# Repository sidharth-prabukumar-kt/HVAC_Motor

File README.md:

# HVAC Motor Project

## Overview

This project is centered around the development of an HVAC motor using a custom-designed motor controller PCB, crafted with KiCAD. The core of the software architecture is built on Zephyr RTOS, tailored with a customized device tree for optimal performance with the STM32 microcontroller.

## Features

- **Motor Control**: Utilizes PWM lines controlled by timer peripherals, interfacing with the TI *DRV8313* motor driver to manage a three-phase motor. This setup is enhanced with feedback mechanisms through current sense resistors and ADC, alongside hall effect sensors.
- **Temperature Regulation**: Incorporates a *LM75B* temperature sensor for data acquisition via I2C, regulating a surface's temperature. This surface is heated using a filament for testing purposes, simulating a real-world application.
- **Fan Implementation**: The three-phase motor is specifically deployed to drive a fan. This fan plays a role in cooling the aforementioned surface, ensuring the system remains within operational thermal limits.
- **Control Systems**: Implements two control systems:
    - A Field Oriented Control (FOC) system, leveraging feedback from the motor for precise PID loop control.
    - A temperature maintenance system, utilizing feedback from the temperature sensor to ensure the surface temperature remains within a designated range.

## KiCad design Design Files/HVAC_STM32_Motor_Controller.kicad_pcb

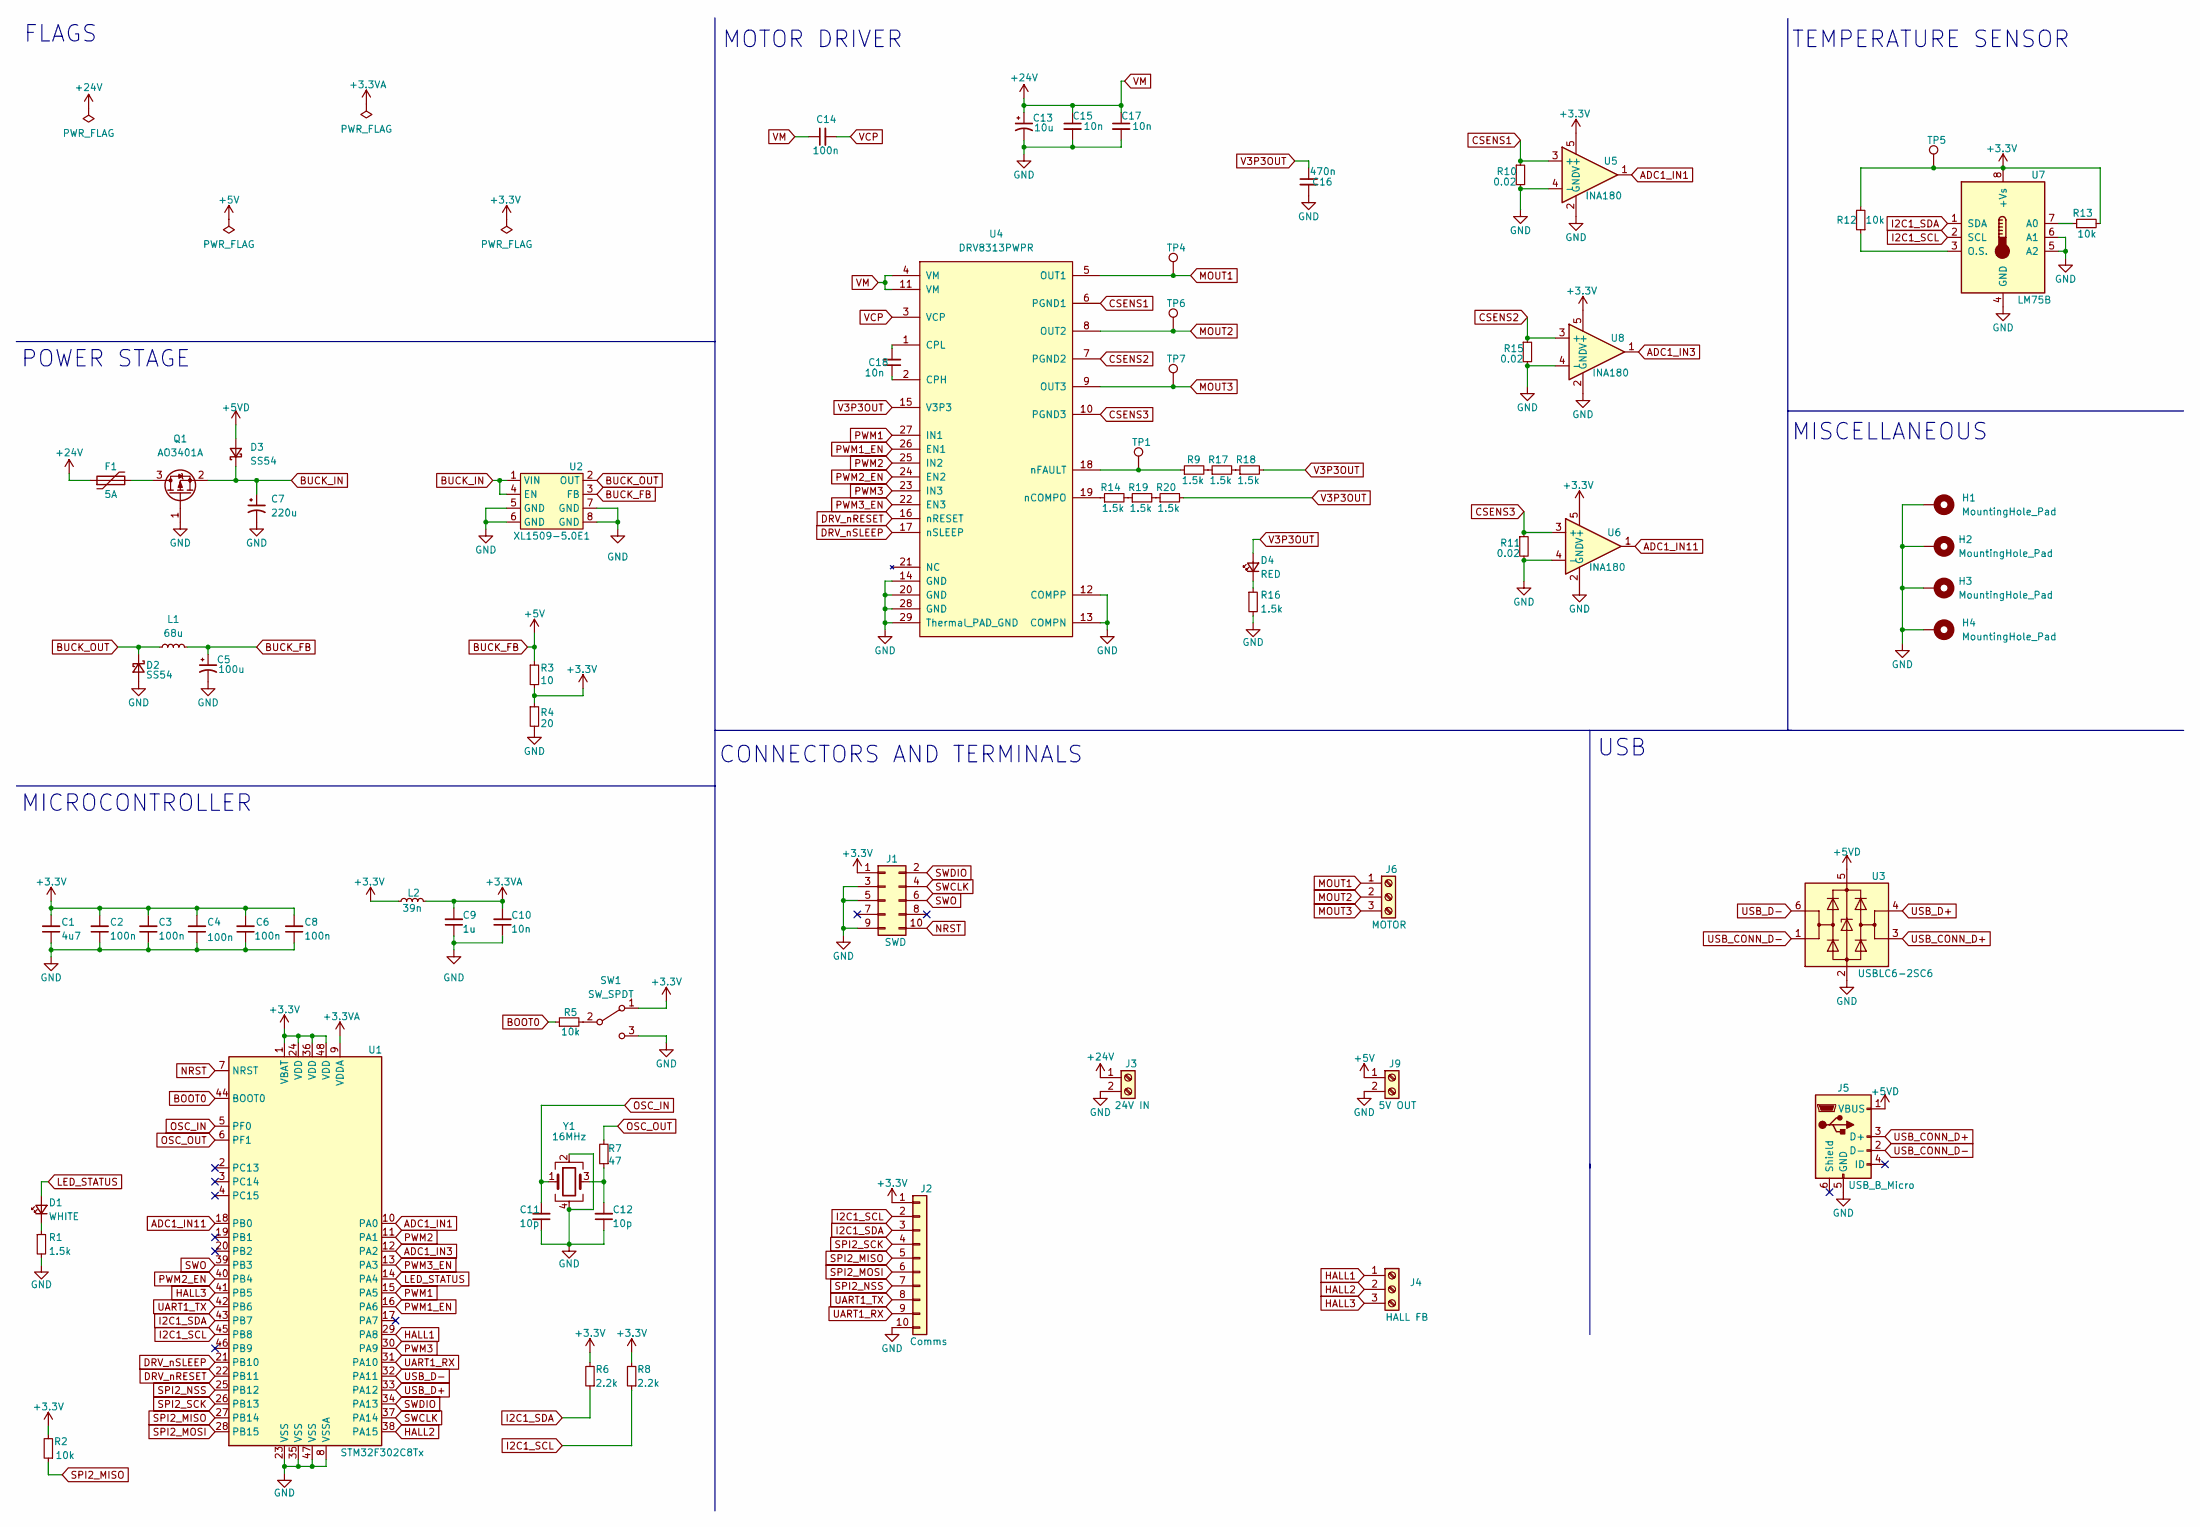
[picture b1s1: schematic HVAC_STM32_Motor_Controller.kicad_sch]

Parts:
C1: 4u7; C_1206_3216Metric; LCSC Part # C29823
C2, C3, C4, C6, C8: 100n; C_0603_1608Metric; LCSC Part # C14663
C5: 100u; CP_Elec_5x5.4; LCSC Part # C2891567
C7: 220u; CP_Elec_10x10.5; LCSC Part # C2887271
C9: 1u; C_0603_1608Metric; LCSC Part # C15849
C10: 10n; C_0603_1608Metric; LCSC Part # C57112
C11, C12: 10p; C_0603_1608Metric; LCSC Part # C1634
C13: 10u; CP_Elec_6.3x5.4; LCSC Part # C2836444
C14: 100n; C_1206_3216Metric; LCSC Part # C24497
C15, C17, C18: 10n; C_1206_3216Metric; LCSC Part # C1846
C16: 470n; C_0603_1608Metric; LCSC Part # C1623
D1: WHITE; LED_0603_1608Metric; LCSC Part # C2290
D2, D3: SS54; D_SMA; LCSC Part # C22452
D4: RED; LED_0603_1608Metric; LCSC Part # C2286
F1: 5A; Fuse_2010_5025Metric; LCSC Part # C48467
H1, H2, H3, H4: MountingHole_Pad; MountingHole_2.2mm_M2_Pad
J1: SWD; IDC-Header_2x05_P2.54mm_Vertical; LCSC Part # C225477
J2: Comms; PinHeader_1x10_P2.54mm_Vertical; LCSC Part # C2905488
J3: 24V IN; TerminalBlock_Altech_AK300-2_P5.00mm; LCSC Part # C3703
J4: HALL FB; TerminalBlock_Altech_AK300-3_P5.00mm; LCSC Part # C8401
J5: USB_B_Micro; USB_Micro-B_Molex-105017-0001; LCSC Part # C10418
J6: MOTOR; TerminalBlock_Altech_AK300-3_P5.00mm; LCSC Part # C8270
J9: 5V OUT; TerminalBlock_Altech_AK300-2_P5.00mm; LCSC Part # C3703
L1: 68u; L_Taiyo-Yuden_NR-30xx; LCSC Part # C83421
L2: 39n; L_0603_1608Metric; LCSC Part # C74308
Q1: AO3401A; SOT-23; LCSC Part # C15127
R1, R9, R14, R16, R17, R18, R19, R20: 1.5k; R_0805_2012Metric; LCSC Part # C4310
R2, R5: 10k; R_0603_1608Metric; LCSC Part # C25804
R3: 10; R_1206_3216Metric; LCSC Part # C17903
R4: 20; R_1206_3216Metric; LCSC Part # C17955
R6, R8: 2.2k; R_0603_1608Metric; LCSC Part # C4190
R7: 47; R_0805_2012Metric; LCSC Part # C17714
R10, R11, R15: 0.02; R_1206_3216Metric; LCSC Part # R1206
R12, R13: 10k; R_1206_3216Metric; LCSC Part # 1206
SW1: SW_SPDT; SW_SPDT_PCM12; LCSC Part # C431541
TP1, TP4, TP5, TP6, TP7: nFAULT; TestPoint_Pad_1.5x1.5mm
U1: STM32F302C8Tx; LQFP-48_7x7mm_P0.5mm; LCSC Part # C90795
U2: XL1509-5.0E1; SOP-8_3.9x4.9mm_P1.27mm; LCSC Part # C61063
U3: USBLC6-2SC6; SOT-23-6; LCSC Part # C2827654
U4: DRV8313PWPR; HTSSOP-28-1EP_4.4x9.7mm_P0.65mm_EP2.85x5.4mm; Tolerance *; Voltage 8-60V; MFR# DRV8313PWPR; LCSC Part # C92482
U5, U6, U8: INA180; SOT-23-5; LCSC Part # SOT-23-5
U7: LM75B; MSOP-8_3x3mm_P0.65mm; LCSC Part # C2837470
Y1: 16MHz; Crystal_SMD_3225-4Pin_3.2x2.5mm

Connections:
+3.3VA: C9.2, C10.2, L2.2, U1.9 (VDDA)
+3V3: C1.2, C2.2, C3.2, C4.2, C6.2, C8.2, J1.1, J2.1, L2.1, R2.2, R3.2, R4.1, R6.2, R8.2, R12.2, R13.2, SW1.1 (A), TP5.1, U1.1 (VBAT), U1.24 (VDD), U1.36 (VDD), U1.48 (VDD), U5.5 (V+), U6.5 (V+), U7.8 (+Vs), U8.5 (V+)
+5VD: D3.2 (A), J5.1 (VBUS), U3.5 (VBUS)
ADC1_IN1: U1.10 (PA0), U5.1
ADC1_IN3: U1.12 (PA2), U8.1
ADC1_IN11: U1.18 (PB0), U6.1
BOOT0: R5.1, U1.44 (BOOT0)
BUCK_FB: C5.1, J9.1, L1.2, R3.1, U2.3 (FB)
BUCK_IN: C7.1, D3.1 (K), Q1.2 (S), U2.1 (VIN), U2.4 (EN)
BUCK_OUT: D2.1 (K), L1.1, U2.2 (OUT)
CSENS1: R10.1, U4.6 (PGND1), U5.3 (+)
CSENS2: R15.1, U4.7 (PGND2), U8.3 (+)
CSENS3: R11.1, U4.10 (PGND3), U6.3 (+)
DRV_nRESET: U1.22 (PB11), U4.16 (nRESET)
DRV_nSLEEP: U1.21 (PB10), U4.17 (nSLEEP)
GND: C1.1, C2.1, C3.1, C4.1, C5.2, C6.1, C7.2, C8.1, C9.1, C10.1, C11.1, C12.1, C13.2, C15.2, C16.2, C17.2, D2.2 (A), H1.1, H2.1, H3.1, H4.1, J1.3, J1.5, J1.9, J2.10, J3.2, J5.5 (GND), J9.2, Q1.1 (G), R1.2, R4.2, R10.2, R11.2, R15.2, R16.2, SW1.3 (C), U1.8 (VSSA), U1.23 (VSS), U1.35 (VSS), U1.47 (VSS), U2.5 (GND), U2.6 (GND), U2.7 (GND), U2.8 (GND), U3.2 (GND), U4.12 (COMPP), U4.13 (COMPN), U4.14 (GND), U4.20 (GND), U4.28 (GND), U4.29 (Thermal_PAD_GND), U5.2 (GND), U5.4 (-), U6.2 (GND), U6.4 (-), U7.4 (GND), U7.5 (A2), U7.6 (A1), U8.2 (GND), U8.4 (-), Y1.2, Y1.4
HALL1: J4.1, U1.29 (PA8)
HALL2: J4.2, U1.38 (PA15)
HALL3: J4.3, U1.41 (PB5)
I2C1_SCL: J2.2, R8.1, U1.45 (PB8), U7.2 (SCL)
I2C1_SDA: J2.3, R6.1, U1.43 (PB7), U7.1 (SDA)
LED_STATUS: D1.2 (A), U1.14 (PA4)
MOUT1: J6.1, TP4.1, U4.5 (OUT1)
MOUT2: J6.2, TP6.1, U4.8 (OUT2)
MOUT3: J6.3, TP7.1, U4.9 (OUT3)
NRST: J1.10, U1.7 (NRST)
unnamed: C12.2, R7.1, Y1.3
unnamed: C18.1, U4.2 (CPH)
unnamed: C18.2, U4.1 (CPL)
unnamed: D1.1 (K), R1.1
unnamed: D4.1 (K), R16.1
unnamed: F1.2, Q1.3 (D)
unnamed: R5.2, SW1.2 (B)
unnamed: R9.1, TP1.1, U4.18 (nFAULT)
unnamed: R12.1, U7.3 (O.S.)
unnamed: R13.1, U7.7 (A0)
unnamed: R14.1, U4.19 (nCOMPO)
unnamed: R14.2, R19.1
unnamed: R9.2, R17.1
unnamed: R17.2, R18.1
unnamed: R19.2, R20.1
OSC_IN: C11.2, U1.5 (PF0), Y1.1
OSC_OUT: R7.2, U1.6 (PF1)
PWM1: U1.15 (PA5), U4.27 (IN1)
PWM1_EN: U1.16 (PA6), U4.26 (EN1)
PWM2: U1.11 (PA1), U4.25 (IN2)
PWM2_EN: U1.40 (PB4), U4.24 (EN2)
PWM3: U1.30 (PA9), U4.23 (IN3)
PWM3_EN: U1.13 (PA3), U4.22 (EN3)
SPI2_MISO: J2.5, R2.1, U1.27 (PB14)
SPI2_MOSI: J2.6, U1.28 (PB15)
SPI2_NSS: J2.7, U1.25 (PB12)
SPI2_SCK: J2.4, U1.26 (PB13)
SWCLK: J1.4, U1.37 (PA14)
SWDIO: J1.2, U1.34 (PA13)
SWO: J1.6, U1.39 (PB3)
UART1_RX: J2.9, U1.31 (PA10)
UART1_TX: J2.8, U1.42 (PB6)
USB_CONN_D+: J5.3 (D+), U3.3 (I/O2)
USB_CONN_D-: J5.2 (D-), U3.1 (I/O1)
USB_D+: U1.33 (PA12), U3.4 (I/O2)
USB_D-: U1.32 (PA11), U3.6 (I/O1)
V3P3OUT: C16.1, D4.2 (A), R18.2, R20.2, U4.15 (V3P3)
VCP: C14.2, U4.3 (VCP)
VM: C13.1, C14.1, C15.1, C17.1, F1.1, J3.1, U4.4 (VM), U4.11 (VM)

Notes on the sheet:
TEMPERATURE SENSOR
MISCELLANEOUS
POWER STAGE
MICROCONTROLLER
USB
CONNECTORS AND TERMINALS
FLAGS
MOTOR DRIVER

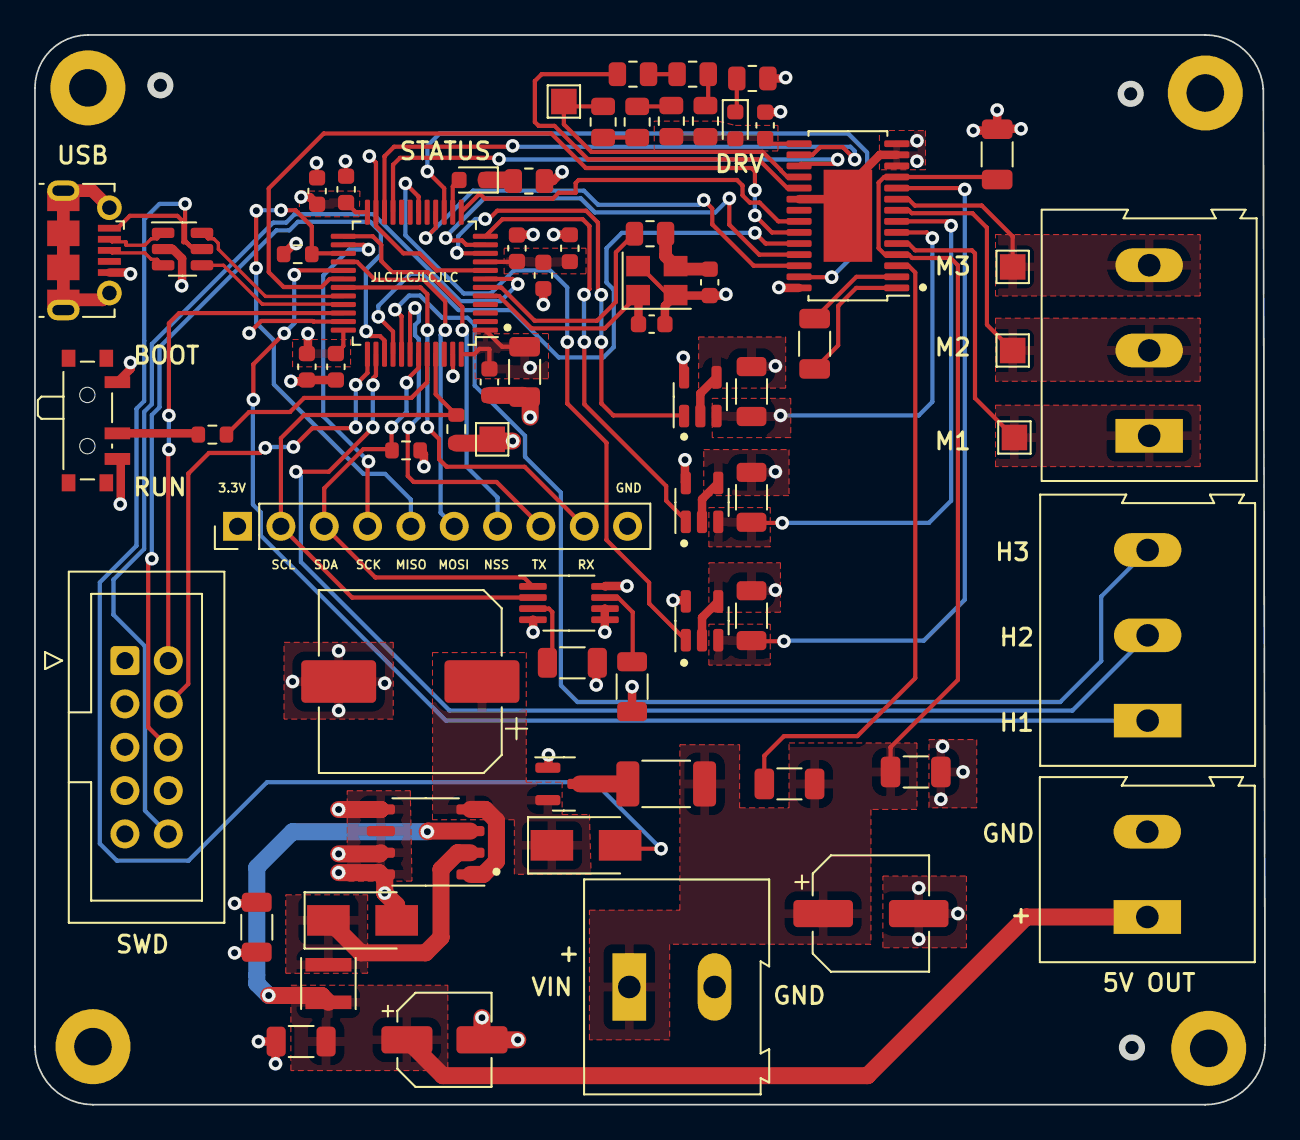
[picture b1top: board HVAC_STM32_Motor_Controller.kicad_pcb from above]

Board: 4 copper layers, 71.8 x 62.4 mm, 72 parts (0 on the bottom side), 65 nets.

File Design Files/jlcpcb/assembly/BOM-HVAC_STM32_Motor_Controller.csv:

Comment,Designator,Footprint,LCSC
10k,"R12,R13",R_1206_3216Metric,1206
USB_B_Micro,J5,USB_Micro-B_Molex-105017-0001,C10418
100n,"C2,C3,C4,C6,C8",C_0603_1608Metric,C14663
AO3401A,Q1,SOT-23,C15127
1u,C9,C_0603_1608Metric,C15849
470n,C16,C_0603_1608Metric,C1623
10p,"C11,C12",C_0603_1608Metric,C1634
47,R7,R_0805_2012Metric,C17714
10,R3,R_1206_3216Metric,C17903
20,R4,R_1206_3216Metric,C17955
10n,"C15,C17,C18",C_1206_3216Metric,C1846
SS54,"D2,D3",D_SMA,C22452
SWD,J1,IDC-Header_2x05_P2.54mm_Vertical,C225477
RED,D4,LED_0603_1608Metric,C2286
WHITE,D1,LED_0603_1608Metric,C2290
100n,C14,C_1206_3216Metric,C24497
10k,"R2,R5",R_0603_1608Metric,C25804
USBLC6-2SC6,U3,SOT-23-6,C2827654
10u,C13,CP_Elec_6.3x5.4,C2836444
LM75B,U7,MSOP-8_3x3mm_P0.65mm,C2837470
220u,C7,CP_Elec_10x10.5,C2887271
100u,C5,CP_Elec_5x5.4,C2891567
Comms,J2,PinHeader_1x10_P2.54mm_Vertical,C2905488
4u7,C1,C_1206_3216Metric,C29823
24V IN,"J3,J9",TerminalBlock_Altech_AK300-2_P5.00mm,C3703
2.2k,"R6,R8",R_0603_1608Metric,C4190
1.5k,"R1,R14,R16,R17,R18,R19,R20,R9",R_0805_2012Metric,C4310
SW_SPDT,SW1,SW_SPDT_PCM12,C431541
5A,F1,Fuse_2010_5025Metric,C48467
10n,C10,C_0603_1608Metric,C57112
XL1509-5.0E1,U2,SOP-8_3.9x4.9mm_P1.27mm,C61063
39n,L2,L_0603_1608Metric,C74308
MOTOR,J6,TerminalBlock_Altech_AK300-3_P5.00mm,C8270
68u,L1,L_Taiyo-Yuden_NR-30xx,C83421
HALL FB,J4,TerminalBlock_Altech_AK300-3_P5.00mm,C8401
STM32F302C8Tx,U1,LQFP-48_7x7mm_P0.5mm,C90795
DRV8313PWPR,U4,HTSSOP-28-1EP_4.4x9.7mm_P0.65mm_EP2.85x5.4mm,C92482
0.02,"R10,R11,R15",R_1206_3216Metric,R1206
INA180,"U5,U6,U8",SOT-23-5,SOT-23-5
nFAULT,TP7,TestPoint_Pad_1.5x1.5mm,
nFAULT,TP1,TestPoint_Pad_1.5x1.5mm,
16MHz,Y1,Crystal_SMD_3225-4Pin_3.2x2.5mm,
nFAULT,TP6,TestPoint_Pad_1.5x1.5mm,
MountingHole_Pad,H2,MountingHole_2.2mm_M2_Pad,
MountingHole_Pad,H3,MountingHole_2.2mm_M2_Pad,
MountingHole_Pad,H4,MountingHole_2.2mm_M2_Pad,
nFAULT,TP4,TestPoint_Pad_1.5x1.5mm,
nFAULT,TP5,TestPoint_Pad_1.5x1.5mm,
MountingHole_Pad,H1,MountingHole_2.2mm_M2_Pad,

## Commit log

2023-05-19 Initial Commit: UART echo
2023-05-28 PWM Test
2024-02-19 Add PCB schematics and design files
2024-02-19 Remove unnecessary design files
